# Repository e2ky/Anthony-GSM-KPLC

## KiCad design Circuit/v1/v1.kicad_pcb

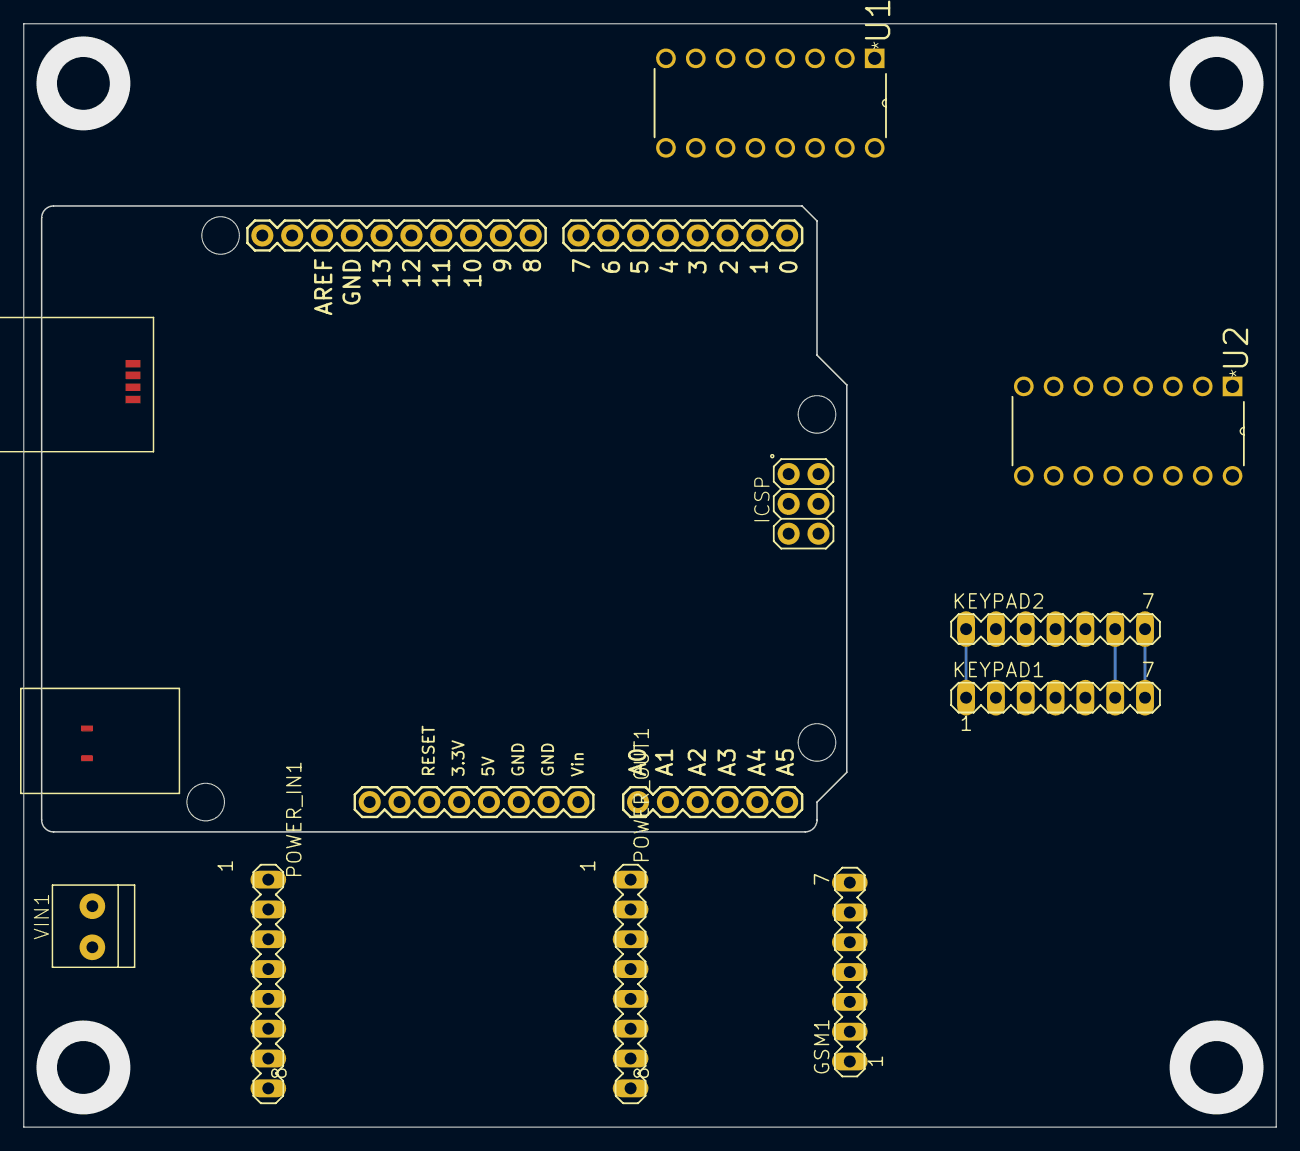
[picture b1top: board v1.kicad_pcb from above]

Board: 2 copper layers, 106.6 x 93.9 mm, 9 parts (0 on the bottom side), 19 nets.

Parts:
GSM1: MA07-1
KEYPAD1, KEYPAD2: MA07-1
PCB1: ARDUINO_UNO
POWER_IN1: MA08-1
POWER_OUT1: MA08-1
U1, U2: CD4051BE; DIP254P762X508-16
VIN1: 1X2-3.5MM

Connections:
/2: PCB1.2, U1.11
/3: PCB1.3, U1.10
/4: PCB1.4, U1.9
/5: PCB1.5, U2.11
/6: PCB1.6, U2.10
/7: PCB1.7, U2.9
/12V: POWER_IN1.1, VIN1.1
/COL1: KEYPAD1.5, KEYPAD2.5, U2.13
/COL2: KEYPAD1.6, KEYPAD2.6, U2.14
/COL3: KEYPAD1.7, KEYPAD2.7, U2.15
/COM: U1.3, U2.3
/GND: GSM1.2, GSM1.6, PCB1.GND., PCB1.GND.., POWER_IN1.8, POWER_OUT1.8, U1.6, U1.7, U1.8, U2.6, U2.7, U2.8, VIN1.2
/ROW1: KEYPAD1.1, KEYPAD2.1, U1.13
/ROW2: KEYPAD1.2, KEYPAD2.2, U1.14
/ROW3: KEYPAD1.3, KEYPAD2.3, U1.15
/ROW4: KEYPAD1.4, KEYPAD2.4, U1.12
/RX: GSM1.3, PCB1.9
/TX: GSM1.4, PCB1.8
/VCC: GSM1.7, PCB1.VIN, POWER_OUT1.1, U1.16, U2.16

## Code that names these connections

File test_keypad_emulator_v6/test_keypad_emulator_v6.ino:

/*
    Arduino Uno Keypad Emulation
    By:- Kim
    Date: 19-06-2021
*/

char inChar;     // setup  for data storage

boolean newData = false;

int col1 = 4;
int col2 = 5;
int col3 = 6;
int row1 = 7;
int row2 = 8;
int row3 = 9;
int row4 = 10;

void setup() 
{
  Serial.begin(9600);

  Serial.println("Initializing...");
  delay(1000);

  //set all pins as outputs
  pinMode (col1, OUTPUT);
  pinMode (col2, OUTPUT);
  pinMode (col3, OUTPUT);
  pinMode (row1, OUTPUT);
  pinMode (row2, OUTPUT);
  pinMode (row3, OUTPUT);
  pinMode (row4, OUTPUT);

}

void loop()
{
  recvData();
}

void recvData()
{
  while (Serial.available())
  {
    inChar = (char)Serial.read();     // get new byte
    emulate();
  }
}

void emulate()
{
  Serial.print("Emulating...");
  Serial.write(inChar);
  switch (inChar)
  {
    case 1:
      digitalWrite (col1, HIGH);
      digitalWrite (col2, LOW);
      digitalWrite (col3, LOW);
      digitalWrite (row1, HIGH);
      digitalWrite (row2, LOW);
      digitalWrite (row3, LOW);
      digitalWrite (row4, LOW);
      break;

    case 2:
      digitalWrite (col1, LOW);
      digitalWrite (col2, HIGH);
      digitalWrite (col3, LOW);
      digitalWrite (row1, HIGH);
      digitalWrite (row2, LOW);
      digitalWrite (row3, LOW);
      digitalWrite (row4, LOW);
      break;

    case 3:
      digitalWrite (col1, LOW);
      digitalWrite (col2, LOW);
      digitalWrite (col3, HIGH);
      digitalWrite (row1, HIGH);
      digitalWrite (row2, LOW);
      digitalWrite (row3, LOW);
      digitalWrite (row4, LOW);
      break;

    case 4:
      digitalWrite (col1, HIGH);
      digitalWrite (col2, LOW);
      digitalWrite (col3, LOW);
      digitalWrite (row1, LOW);
      digitalWrite (row2, HIGH);
      digitalWrite (row3, LOW);
      digitalWrite (row4, LOW);
      break;

    case 5:
      digitalWrite (col1, LOW);
      digitalWrite (col2, HIGH);
      digitalWrite (col3, LOW);
      digitalWrite (row1, LOW);
      digitalWrite (row2, HIGH);
      digitalWrite (row2, LOW);
      digitalWrite (row3, LOW);
      digitalWrite (row4, LOW);
      break;

    case 6:
      digitalWrite (col1, LOW);
      digitalWrite (col2, LOW);
      digitalWrite (col3, HIGH);
      digitalWrite (row1, LOW);
      digitalWrite (row2, HIGH);
      digitalWrite (row3, LOW);
      digitalWrite (row4, LOW);
      break;

    case 7:
      digitalWrite (col1, HIGH);
      digitalWrite (col2, LOW);
      digitalWrite (col3, LOW);
      digitalWrite (row1, LOW);
      digitalWrite (row2, LOW);
      digitalWrite (row3, HIGH);
      digitalWrite (row4, LOW);
      break;

    case 8:
      digitalWrite (col1, LOW);
      digitalWrite (col2, HIGH);
      digitalWrite (col3, LOW);
      digitalWrite (row1, LOW);
      digitalWrite (row2, LOW);
      digitalWrite (row3, HIGH);
      digitalWrite (row4, LOW);
      break;

    case 9:
      digitalWrite (col1, LOW);
      digitalWrite (col2, LOW);
      digitalWrite (col3, HIGH);
      digitalWrite (row1, LOW);
      digitalWrite (row2, LOW);
      digitalWrite (row3, HIGH);
      digitalWrite (row4, LOW);
      break;

    case '*':
      digitalWrite (col1, HIGH);
      digitalWrite (col2, LOW);
      digitalWrite (col3, LOW);
      digitalWrite (row1, LOW);
      digitalWrite (row2, LOW);
      digitalWrite (row3, LOW);
      digitalWrite (row4, HIGH);
      break;

    case 0:
      digitalWrite (col1, LOW);
      digitalWrite (col2, HIGH);
      digitalWrite (col3, LOW);
      digitalWrite (row1, LOW);
      digitalWrite (row2, LOW);
      digitalWrite (row3, LOW);
      digitalWrite (row4, HIGH);
      break;

    case '#':
      digitalWrite (col1, LOW);
      digitalWrite (col2, LOW);
      digitalWrite (col3, HIGH);
      digitalWrite (row1, LOW);
      digitalWrite (row2, LOW);
      digitalWrite (row3, LOW);
      digitalWrite (row4, HIGH);
      break;

  }
  delay (10);
}

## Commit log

2020-08-07 initial
2020-11-18 keypad emulation code'
2021-05-05 serial read and parse
2021-09-29 Improved test code
2021-09-29 Better? sms test code
2021-09-29 Keypad emulation test code
2021-09-29 Final code?
2021-09-29 Circuit moved from breadboard, done in Eagle and include png for milling on modela 1/64 for trace milling and 1/32 for drill holes and outline
2021-10-15 v0 smaller and removed KiCAD files
2021-11-13 circuit for fabrication
2021-12-15 final code
